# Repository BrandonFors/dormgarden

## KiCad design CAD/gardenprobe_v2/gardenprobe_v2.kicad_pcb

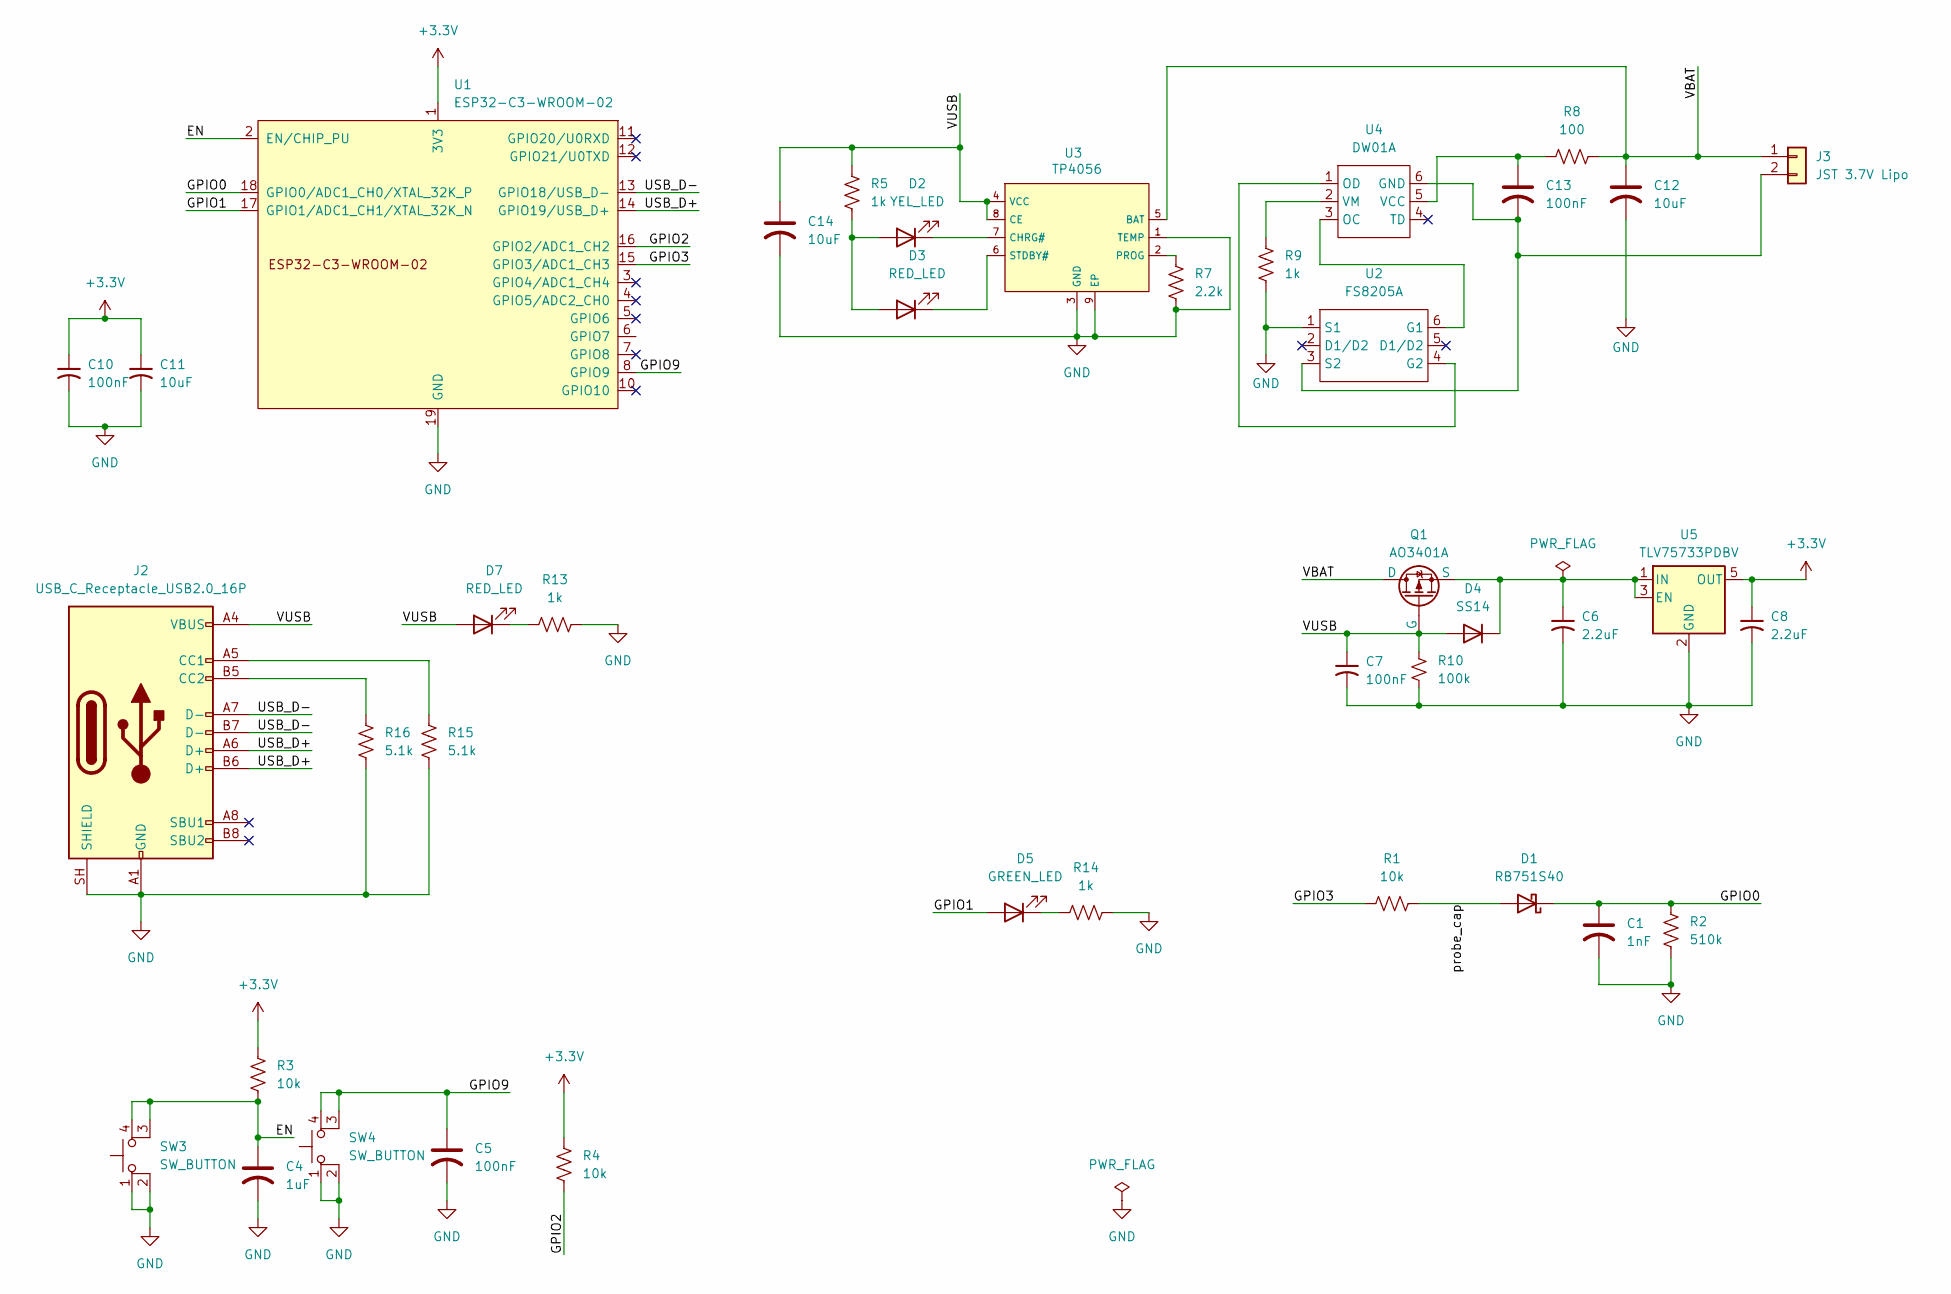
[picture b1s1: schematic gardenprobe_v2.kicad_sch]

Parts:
C1: 1nF; C_0603_1608Metric; LCSC C1588
C4: 1uF; C_0603_1608Metric; LCSC C15849
C5, C7, C10, C13: 100nF; C_0603_1608Metric; LCSC C14663
C6, C8: 2.2uF; C_0603_1608Metric; LCSC C23630
C11, C12, C14: 10uF; C_0603_1608Metric; LCSC C96446
D1: RB751S40; D_SOD-523; LCSC C232576
D2: YEL_LED; D_0603_1608Metric; LCSC C2290
D3, D7: RED_LED; D_0603_1608Metric; LCSC C2286
D4: SS14; D_DO-214AC(SMA); LCSC C2480
D5: GREEN_LED; D_0805_2012Metric; LCSC C2297
J2: USB_C_Receptacle_USB2.0_16P; USB_C_Receptacle_GCT_USB4105-xx-A_16P_TopMnt_Horizontal; LCSC C2765186
J3: JST 3.7V Lipo; JST_PH_B2B-PH-SM4-TB_1x02-1MP_P2.00mm_Vertical; LCSC C160352
Q1: AO3401A; SOT-23; LCSC C20917
R1, R3, R4: 10k; R_0603_1608Metric; LCSC C25804
R2: 510k; R_0603_1608Metric; LCSC C23192
R5, R9, R13, R14: 1k; R_0603_1608Metric; LCSC C21190
R7: 2.2k; R_0603_1608Metric; LCSC C4190
R8: 100; R_0603_1608Metric; LCSC C22775
R10: 100k; R_0603_1608Metric; LCSC C25803
R15, R16: 5.1k; R_0603_1608Metric; LCSC C23186
SW3, SW4: SW_BUTTON; SW-SMD_4P-L5.1-W5.1-P3.70-LS6.5-TL-2; LCSC C318884
U1: ESP32-C3-WROOM-02; LCSC C2934560
U2: FS8205A; SOT-23-6; LCSC C908265
U3: TP4056; ESOP-8_L4.9-W3.9-P1.27-LS6.0-BL-EP; LCSC C382139
U4: DW01A; SOT-23-6; LCSC C351410
U5: TLV75733PDBV; SOT-23-5; LCSC C485517

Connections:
+3.3V: C8.1, C10.1, C11.1, R3.1, R4.1, U1.1 (3V3), U5.5 (OUT)
/EN: C4.1, R3.2, SW3.3 (K), SW3.4 (A), U1.2 (EN/CHIP_PU)
/GPIO0: C1.1, D1.1 (K), R2.1, U1.18 (GPIO0/ADC1_CH0/XTAL_32K_P)
/GPIO1: D5.2 (A), U1.17 (GPIO1/ADC1_CH1/XTAL_32K_N)
/GPIO2: R4.2, U1.16 (GPIO2/ADC1_CH2)
/GPIO3: R1.1, U1.15 (GPIO3/ADC1_CH3)
/GPIO9: C5.1, SW4.3 (K), SW4.4 (A), U1.8 (GPIO9)
/USB_D+: J2.A6 (D+), J2.B6 (D+), U1.14 (GPIO19/USB_D+)
/USB_D-: J2.A7 (D-), J2.B7 (D-), U1.13 (GPIO18/USB_D-)
/VBAT: C12.1, J3.1, Q1.3 (D), R8.2, U3.5 (BAT)
/VUSB: C7.1, C14.1, D4.2 (A), D7.2 (A), J2.A4 (VBUS), J2.A9 (VBUS), J2.B4 (VBUS), J2.B9 (VBUS), Q1.1 (G), R5.2, R10.1, U3.4 (VCC), U3.8 (CE)
/probe_cap: D1.2 (A), R1.2
GND: C1.2, C4.2, C5.2, C6.2, C7.2, C8.2, C10.2, C11.2, C12.2, C14.2, J2.A1 (GND), J2.A12 (GND), J2.B1 (GND), J2.B12 (GND), J2.SH (SHIELD), R2.2, R7.1, R9.1, R10.2, R13.2, R14.2, R15.2, R16.2, SW3.1, SW3.2, SW4.1, SW4.2, U1.9 (GND), U1.19 (GND), U2.1 (S1), U3.1 (TEMP), U3.3 (GND), U3.9 (EP), U5.2 (GND)
unnamed: D2.2 (A), D3.2 (A), R5.1
unnamed: D2.1 (K), U3.7 (CHRG#)
unnamed: D3.1 (K), U3.6 (STDBY#)
unnamed: C6.1, D4.1 (K), Q1.2 (S), U5.1 (IN), U5.3 (EN)
unnamed: D5.1 (K), R14.1
unnamed: D7.1 (K), R13.1
unnamed: J2.A5 (CC1), R15.1
unnamed: J2.B5 (CC2), R16.1
unnamed: C13.2, J3.2, U2.3 (S2), U4.6 (GND)
unnamed: U2.6 (G1), U4.3 (OC)
unnamed: U2.4 (G2), U4.1 (OD)
unnamed: R7.2, U3.2 (PROG)
unnamed: C13.1, R8.1, U4.5 (VCC)
unnamed: R9.2, U4.2 (VM)

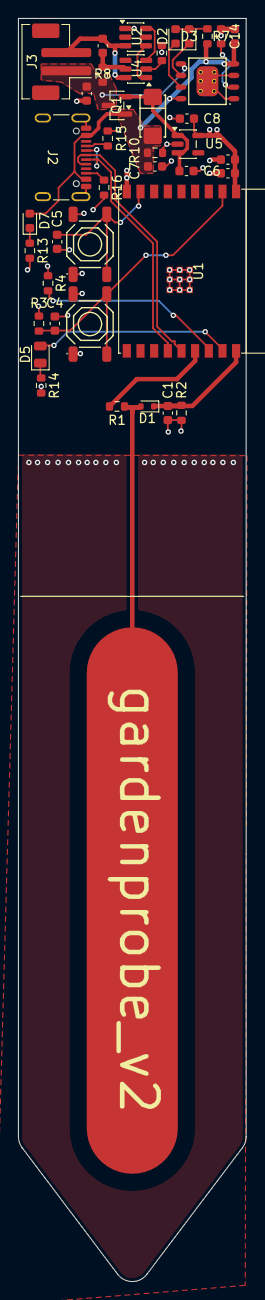
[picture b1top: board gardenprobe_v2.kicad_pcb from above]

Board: 4 copper layers, 25.0 x 138.7 mm, 40 parts (0 on the bottom side), 27 nets.

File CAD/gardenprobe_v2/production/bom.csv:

Designator,Footprint,Quantity,Value,LCSC Part #
C1,0603,1,1nF,C1588
"C10, C13, C5, C7",0603,4,100nF,C14663
"C11, C12, C14",0603,3,10uF,C96446
C4,0603,1,1uF,C15849
"C6, C8",0603,2,2.2uF,C23630
D1,D_SOD-523,1,RB751S40,C232576
D2,0603,1,YEL_LED,C2290
"D3, D7",0603,2,RED_LED,C2286
D4,D_DO-214AC(SMA),1,SS14,C2480
D5,0805,1,GREEN_LED,C2297
J2,USB_C_Receptacle_GCT_USB4105-xx-A_16P_TopMnt_Horizontal,1,USB_C_Receptacle_USB2.0_16P,C2765186
J3,JST_PH_B2B-PH-SM4-TB_1x02-1MP_P2.00mm_Vertical,1,JST 3.7V Lipo,C160352
Q1,SOT-23,1,AO3401A,C20917
"R1, R3, R4",0603,3,10k,C25804
R10,0603,1,100k,C25803
"R13, R14, R5, R9",0603,4,1k,C21190
"R15, R16",0603,2,5.1k,C23186
R2,0603,1,510k,C23192
R7,0603,1,2.2k,C4190
R8,0603,1,100,C22775
"SW3, SW4",SW-SMD_4P-L5.1-W5.1-P3.70-LS6.5-TL-2,2,SW_BUTTON,C318884
U1,ESP32-C3-WROOM-02,1,ESP32-C3-WROOM-02,C2934560
U2,SOT-23-6,1,FS8205A,C908265
U3,ESOP-8_L4.9-W3.9-P1.27-LS6.0-BL-EP,1,TP4056,C382139
U4,SOT-23-6,1,DW01A,C351410
U5,SOT-23-5,1,TLV75733PDBV,C485517
